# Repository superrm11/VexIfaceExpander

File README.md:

# Vex Interface Expansion Board

This project aims to create a board that breaks out a smart port to both Qwiic Connector (I2C) and Mikrobus, for additional expansion to the V5 ecosystem.

This project is a work in progress and is not ready for testing yet.

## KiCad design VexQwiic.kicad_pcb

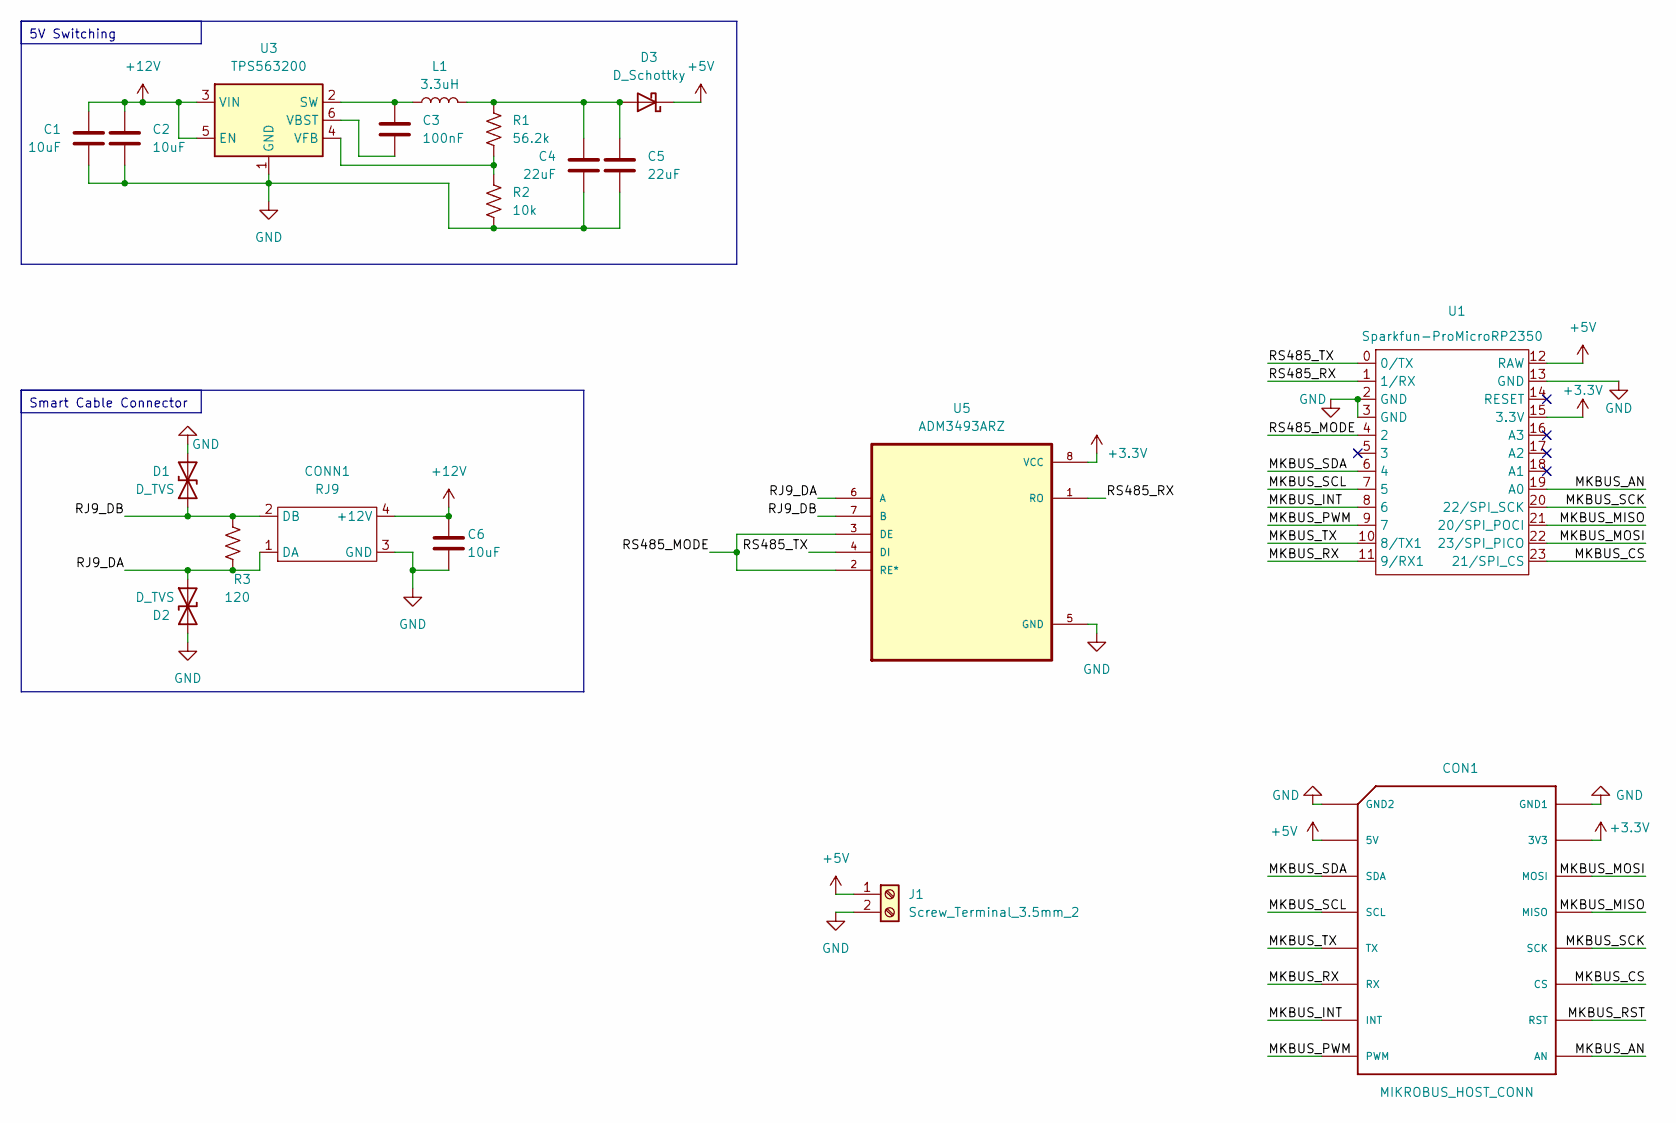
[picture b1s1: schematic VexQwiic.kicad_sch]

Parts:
C1, C2, C6: 10uF; C_0603_1608Metric
C3: 100nF; C_0603_1608Metric
C4, C5: 22uF; C_0603_1608Metric
CON1: MIKROBUS_HOST_CONN
CONN1: RJ9; RJ9_Jack
D1, D2: D_TVS; D_SMA_Handsoldering
D3: D_Schottky; D_SOD-323_HandSoldering
J1: Screw_Terminal_3.5mm_2; Screw_Terminal_3.5mm-2
L1: 3.3uH; BWVS00505040
R1: 56.2k; R_0603_1608Metric
R2: 10k; R_0603_1608Metric
R3: 120; R_0603_1608Metric
U1: Sparkfun-ProMicroRP2350; Sparkfun-ProMicro2350
U3: TPS563200; SOT-23-6
U5: ADM3493ARZ; SOIC127P600X175-8N

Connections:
+3.3V: CON1.P7 (3V3), U1.15 (3.3V), U5.8 (VCC)
+5V: CON1.P10 (5V), D3.1 (K), J1.1, U1.12 (RAW)
+12V: C1.1, C2.1, C6.1, CONN1.4 (+12V), U3.3 (VIN), U3.5 (EN)
/MKBUS_AN: CON1.P1 (AN), U1.19 (A0)
/MKBUS_CS: CON1.P3 (CS), U1.23 (21/SPI_CS)
/MKBUS_INT: CON1.P15 (INT), U1.8 (6)
/MKBUS_MISO: CON1.P5 (MISO), U1.21 (20/SPI_POCI)
/MKBUS_MOSI: CON1.P6 (MOSI), U1.22 (23/SPI_PICO)
/MKBUS_PWM: CON1.P16 (PWM), U1.9 (7)
/MKBUS_RST: CON1.P2 (RST)
/MKBUS_RX: CON1.P14 (RX), U1.11 (9/RX1)
/MKBUS_SCK: CON1.P4 (SCK), U1.20 (22/SPI_SCK)
/MKBUS_SCL: CON1.P12 (SCL), U1.7 (5)
/MKBUS_SDA: CON1.P11 (SDA), U1.6 (4)
/MKBUS_TX: CON1.P13 (TX), U1.10 (8/TX1)
/RJ9_DA: CONN1.1 (DA), D2.1 (A1), R3.2, U5.6 (A)
/RJ9_DB: CONN1.2 (DB), D1.1 (A1), R3.1, U5.7 (B)
/RS485_MODE: U1.4 (2), U5.2 (RE*), U5.3 (DE)
/RS485_RX: U1.1 (1/RX), U5.1 (RO)
/RS485_TX: U1.0 (0/TX), U5.4 (DI)
GND: C1.2, C2.2, C4.2, C5.2, C6.2, CON1.P8 (GND1), CON1.P9 (GND2), CONN1.3 (GND), D1.2 (A2), D2.2 (A2), J1.2, R2.2, U1.2 (GND), U1.3 (GND), U1.13 (GND), U3.1 (GND), U5.5 (GND)
unnamed: C4.1, C5.1, D3.2 (A), L1.2, R1.1
unnamed: C3.1, L1.1, U3.2 (SW)
unnamed: C3.2, U3.6 (VBST)
unnamed: R1.2, R2.1, U3.4 (VFB)

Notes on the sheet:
5V Switching
Smart Cable Connector

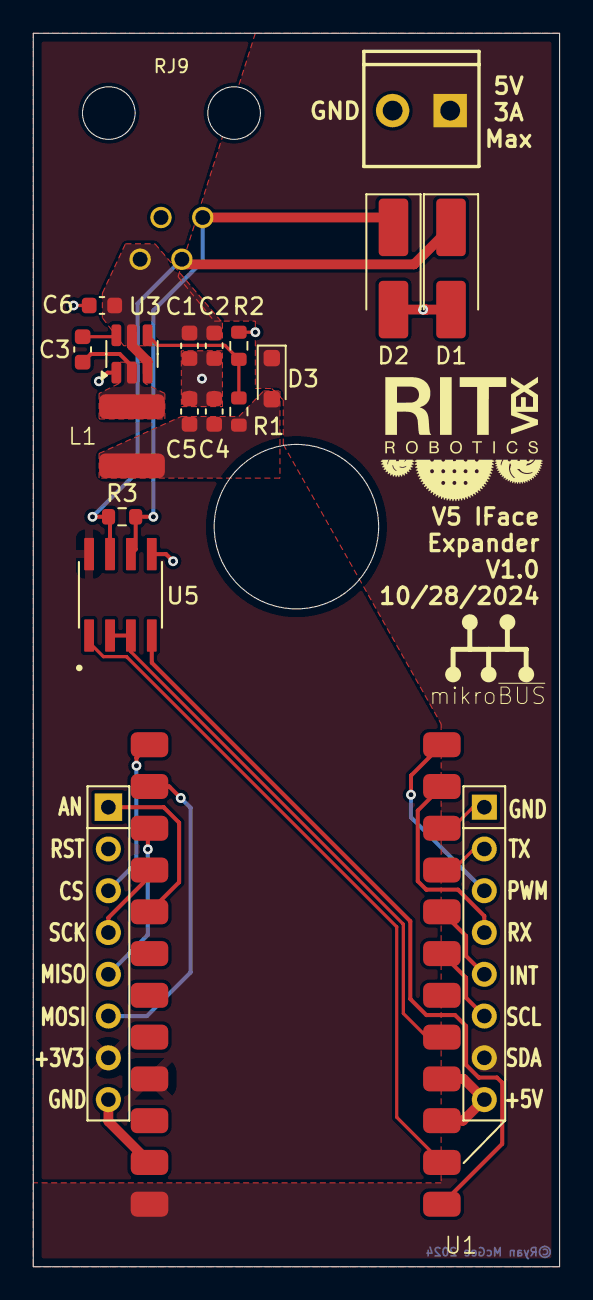
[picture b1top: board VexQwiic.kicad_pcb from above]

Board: 2 copper layers, 32.0 x 75.0 mm, 19 parts (0 on the bottom side), 24 nets.

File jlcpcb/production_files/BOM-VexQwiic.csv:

Comment,Designator,Footprint,LCSC
RJ9,CONN1,RJ9_Jack,
22uF,C4,C_0603_1608Metric,
TPS563200,U3,SOT-23-6,
MIKROBUS_HOST_CONN,CON1,MIKROBUS_HOST_CONN,
100nF,C3,C_0603_1608Metric,
10k,R2,R_0603_1608Metric,
D_TVS,D1,D_SMA_Handsoldering,
D_TVS,D2,D_SMA_Handsoldering,
56.2k,R1,R_0603_1608Metric,
120,R3,R_0603_1608Metric,
10uF,C2,C_0603_1608Metric,
10uF,C1,C_0603_1608Metric,
10uF,C6,C_0603_1608Metric,
D_Schottky,D3,D_SOD-323_HandSoldering,
3.3uH,L1,BWVS00505040,
22uF,C5,C_0603_1608Metric,
Sparkfun-ProMicroRP2350,U1,Sparkfun-ProMicro2350,
ADM3493ARZ,U5,SOIC127P600X175-8N,
Screw_Terminal_3.5mm_2,J1,Screw_Terminal_3.5mm-2,

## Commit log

2024-10-16 Initial commit - Not done!
2024-10-16 goofed and didn't add .png extension
2024-10-23 Last version w/ rp2040
2024-10-29 Version 1 complete & ordered.
2024-10-29 Edited formatting

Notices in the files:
VexQwiic.kicad_pcb:
©Ryan McGee 2024
